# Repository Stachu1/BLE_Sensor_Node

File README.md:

# BLE Sensor Node

**BEng in Electronics Engineering thesis project, focused on low-power design and RF performance.**

A compact, coin-cell-powered Bluetooth Low Energy sensor node that measures temperature and humidity and broadcasts
the data as [BTHome](https://bthome.io/) advertisements, without needing a persistent connection.

*Rev B, `BSN-C23-B`: the top with the printed antenna along the upper edge (left) and the back with the coin-cell
holder (right). 34 × 34 mm.*

## Goal

Keep the average current low enough for multi-year operation on a single CR2032 cell, in a compact size. Main areas
of work: low-power firmware and advertising strategy, antenna/RF performance (chip vs. trace antenna), and power
budgeting around the coin cell's current limits.

## Highlights

- **Two MCUs designed, built and measured side by side** on rev A: Nordic nRF54L05 (`BSN-N54`) and TI CC2340R5
  (`BSN-C23`), with the same sensors, antenna and board outline. The CC2340R5 was chosen for rev B, mainly on sleep
  current and with RF performance as a second factor ([`MCU_DECISION.md`](hardware/MCU_DECISION.md)).
- **4.8 µA average at a 5 s advertising interval, measured** on BSN-C23-A, with firmware that sends one advert
  per sensor reading and writes the new reading into the running advert. Every event (advert, sensor reading,
  payload reload, cold boot) was measured as a charge, which gives a current model for any setting. The model
  predicts 4.9 µA for this case. Sleep floor about 0.7 µA. At 4.8 µA a 225 mAh CR2032 would last about 5 years
  before derating ([power measurements](hardware/C23/testing/rev_A/Power/POWER_MEASUREMENTS.md)).
- **Rev A chip antenna matched on the VNA**, step by step from the unmatched antenna, with the board lifted off the
  bench (the wooden table under it had detuned the antenna) ([antenna matching](hardware/C23/testing/rev_A/RF/ANTENNA_MATCHING.md)).
- **Conducted harmonics measured on a spectrum analyser** and compared with ETSI EN 300 328 (−30 dBm, the
  standard for an EU product) and the stricter FCC restricted-band limit (−41.2 dBm). Formal EMC testing is out
  of scope, so the limits are a reference and results are given as margins. With no filter, H3 at 0 dBm is
  10.6 dB under ETSI and 0.6 dB over FCC on the C23, and 5.7 dB over ETSI on the N54. With the simple pi network
  from TI's reference design the C23 keeps at least 9.5 dB to FCC at +8 dBm. Nordic's reference design uses
  0201 parts. The N54 board uses 0402, so the PA network layout had to be adapted, which likely caused its loss
  of about 10 dB of output power. It was bypassed for the measurements ([C23](hardware/C23/testing/rev_A/RF/RF_CARRIER.md), [N54](hardware/N54/testing/RF/RF_CARRIER.md)).
- **Rev B trace antenna designed in openEMS on the real board, then measured.** A scripted pipeline exports the
  KiCad board (all four copper layers, vias, stack-up, the CR2032) to the FDTD solver on a compute server. The
  chosen inverted-F antenna simulated at −14.9 dB S11 or better across the BLE band with two matching parts. On
  the built board the VNA measured −12.1 dB or better with the simulated parts unchanged, with the resonance
  within 1.5 % of the simulated frequency. The simulated total efficiency is 80 to 91 %, not yet measured
  ([antenna write-up](hardware/C23/testing/RF/antenna_C23-B/README.md), [simulation pipeline](hardware/C23/testing/RF/sim/README.md),
  [VNA measurement](hardware/C23/testing/rev_B/RF/ANTENNA_MATCHING.md)).
- **Nine rev B boards hand-assembled and brought up**, all passing the 13-point hardware self-test. Seven
  have been seen advertising BTHome readings, decoded by a PC script. Rev B RF was checked on a spectrum analyser: carrier within
  ±0.7 ppm of the analyser reference on all three advertising channels, harmonics H2 to H4 below −54 dBm
  ([spectrum](hardware/C23/testing/rev_B/RF/SPECTRUM.md)).
- **Firmware for both MCUs** written to the same structure (bring-up self-test, BLE sensor, CW RF test, one power
  state per build) so the two can be measured the same way.

## Design

| `BSN-C23-B` (TI CC2340R5) | `BSN-N54-A` (Nordic nRF54L05) |
|---|---|
|  |  |
| [Schematic](hardware/C23/schematic.pdf) · [PCB](hardware/C23/PCB.pdf) · [README](hardware/C23/README.md) | [Schematic](hardware/N54/schematic.pdf) · [PCB](hardware/N54/PCB.pdf) · [README](hardware/N54/README.md) |

4-layer, 34 × 34 mm board with an HDC2010 temperature/humidity sensor, the CR2032 holder on the back and test
points for SWD, UART, I2C and the sensor interrupt.

- **Rev A (both variants):** 15.5 mm corner radii (close to round), chip antenna with a pi matching network, an
  optional U.FL connector for conducted RF tests and an SHTC3 footprint as an alternative sensor.
- **Rev B (C23 only):** 10 mm corner radii, an inverted-F antenna printed on the top layer, an MM8130 switch
  connector for VNA measurements of the antenna match, a Tag-Connect footprint for SWD, UART TX and a BOOT pin for
  the ROM bootloader, and a 0 Ω link in the supply for the ammeter. The pi network is unchanged from rev A.

## Status

Rev A of both variants was compared (thesis test T0). **Rev B uses the TI CC2340R5 (`BSN-C23-B`)** with a PCB trace
antenna, and the N54 variant stops at rev A. Rev B was ordered on 2026-11-04 (tag `hw/BSN-C23-B`) and assembled
from 2026-11-13. A rev C will only be made if the rev B tests show it is needed and there is time.

Why the CC2340R5:

- **Lower average current at the intervals this node uses.** The N54 needs 40–50 % less charge per advert and per
  reading, but its 4.2 µA sleep floor outweighs that from about a 1.3 s interval upwards. At 5 s the C23 measured
  4.8 µA and the N54 6.1 µA (table below). The C23 got there in two steps. The first full firmware measured 6.5 µA,
  because in the TI stack every payload reload (stopping the advert, loading the new reading, restarting it) costs
  about 20 µC. The firmware was then changed to skip the reload and write each new reading into the running
  advert, which brought it down to 4.83 µA.
- **A working RF chain.** The C23 keeps a margin to the harmonic limits with the simple pi network from TI's
  reference design, so rev B could start from an RF chain that works. The N54 would need a new harmonic filter and
  another RF iteration.
- **A simpler, cheaper part.** A 4 × 4 mm, 24-pin package against 6 × 6 mm and 48 pins for the nRF54L05, and a
  lower unit price.

Together that made the C23 the simpler and lower-risk base for the next revision.

### Rev B results

The antenna match is measured through an MM8130 switch connector between the chip and the antenna. Plugging in
the probe (right) disconnects the chip side, so the VNA sees only the antenna and its two matching parts, with
no parts moved.

*S11 of the rev B antenna at the MM8130 connector. Left: the antenna without matching parts, openEMS simulation
against measurement. Right: with L2 1.6 nH and L3 6.8 nH from the simulation, measured with the board standing on
its battery holder with the cell, the typical placement. Worst S11 in the BLE band (grey) −18.8 dB.*

The antenna is sensitive to what is around it. Lying flat on a table it is detuned by about 330 MHz. A plastic
enclosure close to the antenna would also lower the resonance, so the match would need retuning in the final
housing. The enclosure is out of scope, as this project covers the electronics and not the mechanical design.

| | `BSN-C23-B` | Notes |
|---|---|---|
| Bring-up | 9 boards, all 13/13 in the hardware self-test | Hand-assembled |
| Antenna match, worst S11 in 2.40–2.48 GHz | −12.1 dB in the air, −18.8 dB standing on the battery holder | Simulated −14.9 dB. Lying flat on a table detunes it by about 330 MHz |
| Carrier frequency | Within ±0.7 ppm of the analyser reference | 2402, 2440 and 2480 MHz, no crystal retrim needed |
| Conducted power at the antenna connector | +3.2 dBm at the +8 dBm setting, −3.9 dBm at the 0 dBm setting | Read +2.4 and −4.7 dBm, corrected for the 0.84 dB probe loss measured on the VNA |
| Harmonics at +8 dBm, conducted | H2 to H4 below −54 dBm. H5 −40.9 dBm: 10.9 dB under ETSI, 0.3 dB under FCC | Probe loss not corrected, the true level is higher. H5 is about 10 dB worse than rev A with the same filter parts, cause not investigated |
| Supply current, continuous carrier at 3.0 V | 6.14 mA at 0 dBm, 14.20 mA at +8 dBm | Sets the coin-cell budget for a radiated test |

Details: [`hardware/C23/README.md`](hardware/C23/README.md), [`hardware/C23/testing/rev_B`](hardware/C23/testing/rev_B).

### Rev A comparison

*Rev A: `BSN-N54-A` (left), `BSN-C23-A` (middle) and the back of `BSN-C23-A` with the coin-cell holder.*

| | `BSN-C23-A` | `BSN-N54-A` |
|---|---|---|
| **Average current, 5 s advertising, measured (model)** | **4.83 µA** (4.9 µA). One advert per sensor reading, reading written into the running advert | **6.1 µA** (6.01 µA). Sensor every 10 s |
| Sleep floor | About 0.7 µA (0.70 µA on the no-filter board, the datasheet typical is 0.71 µA. An early 0.37 µA on board #1 did not repeat) | 4.20 µA (System OFF 2.05 µA, both about 1.4 µA above the datasheet, cause not found) |
| Charge per advert, 0 dBm | 12.6 µC | 7.6 µC |
| Charge per sensor reading, timer / DRDY wake | 9.56 / 3.72 µC | 2.01 / 1.78 µC |
| Charge per payload reload | About 20 µC in the TI stack (6.5 µA at 5 s with a reload every 10 s). Later skipped by writing the reading into the running advert | No such cost |
| Conducted power at the 0 dBm setting, no filter (same spectrum analyser setup, cable loss not corrected) | −1.7 dBm (−3.2 dBm with the pi network) | −0.7 dBm (PA network bypassed) |
| Harmonics with no filter, 0 dBm (conducted, worst is H3) | H3 −40.6 dBm: 10.6 dB under ETSI (−30 dBm), 0.6 dB over FCC (−41.2 dBm) | H3 −24.3 dBm: 5.7 dB over ETSI, 17 dB over FCC |
| Harmonic filter | Pi network from TI's reference design. At +8 dBm (2440 and 2480 MHz) at least 9.5 dB under FCC (H5) | Nordic's reference design uses 0201 parts, this board uses 0402, so the PA network layout was adapted. It lost 10–11 dB of output power, likely because of the adapted layout, and was bypassed. No working filter on this layout |
| Notes | [`hardware/C23/testing`](hardware/C23/testing) | [`hardware/N54/testing`](hardware/N54/testing) |

Rev A boards:

| Board | MCU | Status |
|---|---|---|
| `BSN-N54-A` | nRF54L05 | Ordered and assembled (2 boards). Board #1 advertising BTHome. Board #2 (U.FL): HFXO trimmed to 11.75 pF, PA network bypassed (the rev A layout of it loses 10 dB), 0.0 dBm at the 0 dBm setting. Floor 4.20 µA, 7.6 µC per advert |
| `BSN-C23-A` | CC2340R5 | Ordered and assembled. Board #1 flashed and advertising BTHome, antenna matched with the board lifted off the bench (L2 4.3 nH, L3 2.1 pF). Floor about 0.7 µA, 12.6 µC per advert, about 20 µC per payload reload in the TI stack, 4.83 µA at 5 s with the reading written into the running advert. CW boards with and without the PA pi network |

Open questions:

- The N54 floor sits about 1.4 µA above the datasheet on both boards. Not needed for the MCU choice, but still being
  looked into for the thesis.

### Next

- **Rev B power:** average current on a real CR2032 at a 5 s interval, the VDD dip during TX, and the battery-life
  projection.
- **Range:** line-of-sight range test of the rev A chip antenna and the rev B trace antenna in one session.
- **Radiated:** pattern, total radiated power and the radiated H5 level in the anechoic chamber at the university,
  if a slot can be arranged.
- **Rev C** (optional): only if rev B needs fixes and time allows.

## Repository Structure

```
hardware/
  MCU_DECISION.md   Why rev B uses the CC2340R5
  C23/              BSN-C23 - TI CC2340R5 variant: KiCad project, schematic/PCB PDFs, testing/
  N54/              BSN-N54 - Nordic nRF54L variant (concluded at rev A)
  N52/              BSN-N52 - Nordic nRF52805 side variant: smaller, CR1632 (rev A)
firmware/
  C23/              Firmware for BSN-C23 boards (TI SimpleLink SDK)
  N54/              Firmware for BSN-N54 boards (nRF Connect SDK)
  N52/              Firmware for BSN-N52 boards (nRF Connect SDK, and a bare-metal beacon)
docs/
  datasheets/       Links to the datasheets and application notes used
  images/           Photos
```

The two MCU candidates are different chips (different pinout, power tree and BOM) rather than build options of one
board, so each has its own KiCad project under `hardware/<variant>/` and its own `firmware/<variant>/`. The N54
folders stay as the record of the rev A comparison. Only the C23 variant continues.
`BSN-N52` is a later side variant outside the original requirements: a smaller, cheaper node on a CR1632
with the same sensor and a printed antenna, see [`hardware/N52/README.md`](hardware/N52/README.md).

Test results live next to the board they were measured on, in `hardware/<variant>/testing/`, with the bring-up
procedures in `firmware/<variant>/BRINGUP.md`. The C23 rev A measurements are in `hardware/C23/testing/rev_A/`, the
rev B antenna simulations in `hardware/C23/testing/RF/`. The schematic and PCB PDFs always show the latest revision of each
board. Older revisions are in the KiCad files at their `hw/BSN-<variant>-<rev>` tags.

## Naming Scheme

Each board is identified as **`BSN-<variant>-<revision>`**, e.g. `BSN-C23-A`.

```
BSN-C23-A
 │   │  └─ PCB revision  (A, B, C …)
 │   └──── MCU variant   (C23 = TI CC2340R5, N54 = Nordic nRF54L, N52 = Nordic nRF52805)
 └──────── Board name    (BSN = BLE Sensor Node)
```

- **Variant:** first letter of the MCU part prefix (**n**RF54 → N, **C**C2340 → C) + MCU family number. Each variant
  has its own revision counter.
- **Revision:** bare-PCB revision, bumped only when new boards are ordered. Once gerbers are sent to the fab that
  letter is frozen. The ordered commit is tagged `hw/BSN-<variant>-<rev>`.
- **Assembly option** *(optional)*, e.g. `-UFL`: a population option on the same bare PCB. Does not change the
  revision.
- **Reworked boards** are marked `A*`, with the rework noted in the variant README.
- **The ID is on the board itself:** set in the KiCad title block and printed on the silkscreen. The firmware board
  target is `BSN_C23` / `BSN_N54` / `bsn_n52`.

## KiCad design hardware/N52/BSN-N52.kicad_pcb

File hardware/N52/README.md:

# BSN-N52 (Nordic nRF52805 variant)

> **Side variant, outside the original requirements.** A smaller, cheaper node, designed as a separate
> project ("AirTag") and moved into this repository on 2026-11-23. It uses the same HDC2010 sensor and a printed
> inverted-F antenna like `BSN-C23-B`, but it is smaller, runs on a CR1632 and probably has worse RF performance.
> It does not replace `BSN-C23-B`. Whether and how it appears in the report is still open.

KiCad project: `BSN-N52.kicad_pro`. See the root README for the board naming scheme. Firmware, bring-up procedure
and per-board results: [`firmware/N52`](../../firmware/N52) and [`firmware/N52/BRINGUP.md`](../../firmware/N52/BRINGUP.md).

[Schematic](schematic.pdf) · [PCB](PCB.pdf)

## Rev A (`BSN-N52-A`)

- **24 × 17 mm**, 2 layers, 1.6 mm, 3 mm corner radius. The CR1632 holder is on the back and the cell overhangs
  the bottom edge.
- **nRF52805-CAAA** (WLCSP-28, 2.48 × 2.46 mm, 192 kB flash, 24 kB RAM) with the DC/DC converter (L3 10 µH), a 32 MHz
  crystal and no 32 kHz crystal (the low-frequency clock is the internal RC).
- **HDC2010** temperature/humidity sensor on I2C with its interrupt line (DRDY) to the SoC. No external I2C
  pull-ups (the nRF internal ones are used).
- **Printed meandered inverted-F antenna (MIFA)** along the top edge in a 20 × 5 mm keep-out, designed in openEMS on
  this board ([`testing/RF/sim`](testing/RF/sim)). Fed through a T network L2 4.7 nH series, C1 0.5 pF shunt,
  L1 8.2 nH series (match and harmonic filter, from the r7 simulation with the solder mask and the cell).
  **No RF connector** (no MM8130 or test port): the antenna and the carrier can only be measured radiated, and the
  matching parts and the 32 MHz crystal load caps are fixed in hardware (no firmware trim).
- **SWD only**: Tag-Connect TC2030-NL (J1) with VCC, SWDIO, RESET, SWCLK, GND. No LED, no UART.
- The silkscreen carries the author's handle, not the board ID. The ID is in the KiCad title block only.

### Parts

| Ref | Part | DigiKey |
|---|---|---|
| U2 | Nordic nRF52805-CAAA (WLCSP-28) | `4823-NRF52805-CAAA-RCT-ND` |
| U1 | TI HDC2010 humidity / temperature sensor | `296-47774-1-ND` |
| X1 | ECS ECS-320-8-37B-CKY-TR, 32 MHz, 8 pF, ±10/±10 ppm, 2.0 × 1.6 mm | `50-ECS-320-8-37B-CKY-TRCT-ND` |
| L3 | Murata LQM18DN100M70L, 10 µH, 0603, DC/DC inductor | `490-LQM18DN100M70LCT-ND` |
| C2 | Cal-Chip GMC21X5R476M6R3NT, 47 µF 6.3 V X5R, 0805, bulk cap | `4713-GMC21X5R476M6R3NTCT-ND` |
| BT1 | CR1632 in Assmann A-BAT-CH-C6-EA-CSR1 (the clip is +, a bare pad under the cell is −) | `123-A-BAT-CH-C6-EA-CSR1CT-ND` |
| L2 / C1 / L1 | RF T network: 4.7 nH / 0.5 pF / 8.2 nH | `490-16635-1-ND` / `490-11250-1-ND` / `490-18131-1-ND` |

The BOM export (`BSN-N52.csv`) and the order sheet (`bom/`) are kept locally like those of the other variants.
The schematic is the source.

### Manufacturing

Ordered on 2026-11-16 as a **3 × 3 panel** (KiKit 1.8.1, [`panel/panel.json`](panel/panel.json)), hand assembled,
so no fiducials or tooling holes. The commit that added this folder is tagged `hw/BSN-N52-A`. The board files are
the ordered ones, only renamed and given a title block.

- 2 mm gaps between boards, 5 mm rails top and bottom only.
- Tabs 2.2 mm wide, mouse bites of 3 × 0.5 mm holes at 0.8 mm pitch, **offset −0.5 mm** so the holes sit in the gap
  and not on the antenna. The boards keep an FR4 nub of about 0.25–0.5 mm after breaking (no copper in it).
- The top-edge tabs sit on the antenna edge. Move them off that edge in a later revision if needed.

Regenerate the panel after a board change (from `hardware/N52`):

```
"C:\Program Files\KiCad\10.0\bin\python.exe" -m kikit.ui panelize -p panel/panel.json BSN-N52.kicad_pcb panel/BSN-N52_panel.kicad_pcb
```

### Bring-up status

Three boards assembled, all pass the 11-point hardware self-test (`hwtest`). Details in
[`firmware/N52/BRINGUP.md`](../../firmware/N52/BRINGUP.md). Parts for about seven more are on hand.

| Board | BLE address | Status |
|---|---|---|
| A #1 | DF:55:EE:37:04:CD | `hwtest` 11/11. Used to develop the tests |
| A #2 | C2:D7:6D:9C:B3:20 | A\*: HDC2010 reworked (SDA and INT held low). Then `hwtest` 11/11, `ble_sensor` flashed |
| A #3 | DB:1C:AA:DB:F2:9D | `hwtest` 11/11, BTHome seen on the scanner. `ble_beacon_min` measured at 1.706 µA average |

### Test results

- **Current:** [`testing/Power/POWER_MEASUREMENTS.md`](testing/Power/POWER_MEASUREMENTS.md). 1.706 µA average at
  the 5 s DRDY interval on A #3 with the bare-metal `ble_beacon_min` (System OFF between adverts), about 2.5 times
  lower than `BSN-C23-B` (4.36 to 4.39 µA). Single reading on the 10 mA range, see the caveats there.
- **RF:** simulated only ([`testing/RF/sim`](testing/RF/sim)). Not measured on a built board yet.

### Rework log

Hand-modified boards are marked `A*` (see the root README).

| Board | Date | Change | Reason |
|---|---|---|---|
| A #2 | by 2026-11-23 | HDC2010 (U1) reworked | First `hwtest` failed: SDA and INT held low by U1 (bad joint or short) |

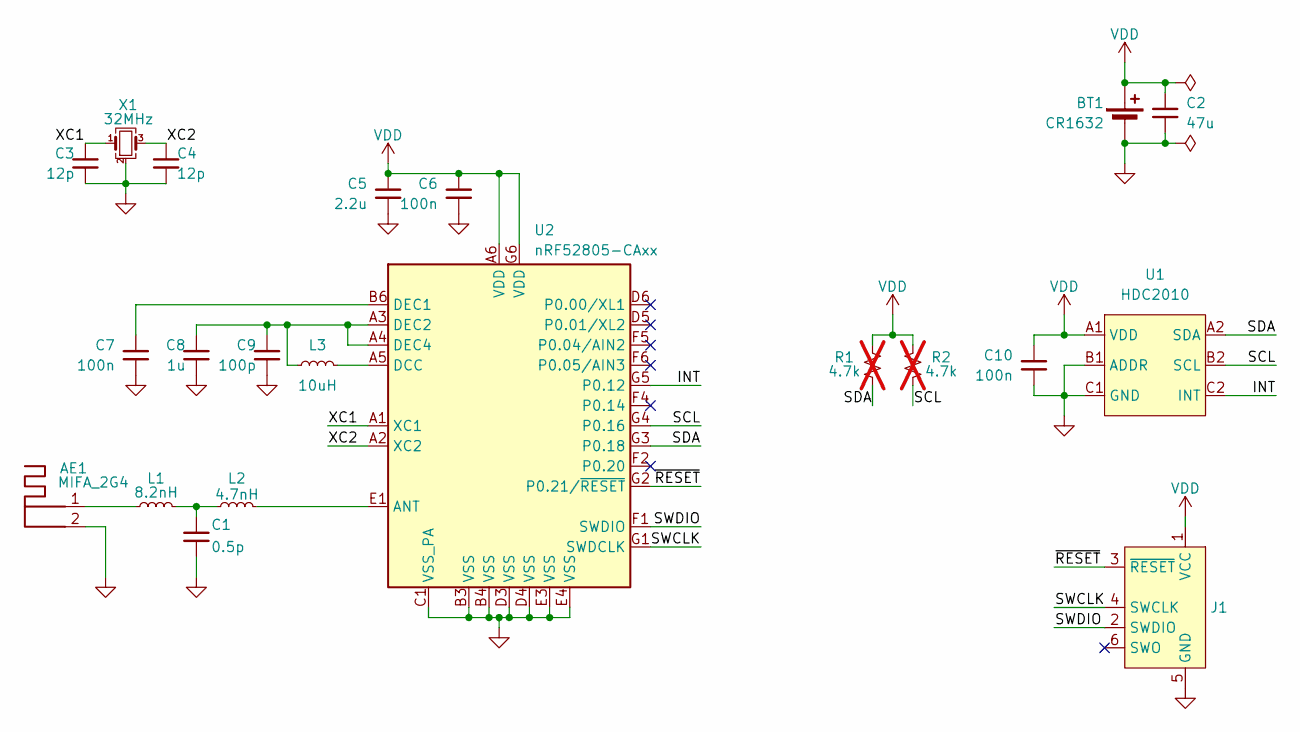
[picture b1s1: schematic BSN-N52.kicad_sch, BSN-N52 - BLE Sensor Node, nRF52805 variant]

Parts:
AE1: MIFA_2G4
BT1: CR1632; BatteryHolder_Assmann_A-BAT-CH-C6-EA-CSR1_CR1632; DigiKey 123-A-BAT-CH-C6-EA-CSR1CT-ND
C1: 0.5p; C_0402_1005Metric; DigiKey 490-11250-1-ND
C2: 47u; C_0805_2012Metric; DigiKey 4713-GMC21X5R476M6R3NTCT-ND
C3, C4: 12p; C_0402_1005Metric; DigiKey 311-1016-1-ND
C5: 2.2u; C_0402_1005Metric; DigiKey 445-9028-1-ND
C6, C7, C10: 100n; C_0402_1005Metric
C8: 1u; C_0402_1005Metric; DigiKey 311-1439-1-ND
C9: 100p; C_0402_1005Metric; DigiKey 311-1024-1-ND
J1: Conn_ARM_SWD_TagConnect_TC2030-NL; Tag-Connect_TC2030-IDC-NL_2x03_P1.27mm_Vertical
L1: 8.2nH; L_0402_1005Metric; DigiKey 490-18131-1-ND
L2: 4.7nH; L_0402_1005Metric; DigiKey 490-16635-1-ND
L3: 10uH; L_0603_1608Metric; DigiKey 490-LQM18DN100M70LCT-ND
R1, R2: 4.7k; R_0402_1005Metric; not fitted
U1: HDC2010; DigiKey 296-47774-1-ND
U2: nRF52805-CAxx; Nordic_nRF52805-CAxx_WLCSP-28_2.482x2.464mm; DigiKey 4823-NRF52805-CAAA-RCT-ND
X1: 32MHz; Crystal_SMD_2016-4Pin_2.0x1.6mm; DigiKey 50-ECS-320-8-37B-CKY-TRCT-ND

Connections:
/INT: U1.C2 (INT), U2.G5 (P0.12)
/SCL: R2.1, U1.B2 (SCL), U2.G4 (P0.16)
/SDA: R1.1, U1.A2 (SDA), U2.G3 (P0.18)
/SWCLK: J1.4 (SWCLK), U2.G1 (SWDCLK)
/SWDIO: J1.2 (SWDIO), U2.F1 (SWDIO)
/XC1: C3.1, U2.A1 (XC1), X1.1
/XC2: C4.1, U2.A2 (XC2), X1.3
/~RESET: J1.3 (~RESET), U2.G2 (P0.21/~RESET)
GND: AE1.2 (GND), BT1.2 (-), C1.2, C2.2, C3.2, C4.2, C5.2, C6.2, C7.2, C8.2, C9.2, C10.2, J1.5 (GND), U1.B1 (ADDR), U1.C1 (GND), U2.B3 (VSS), U2.B4 (VSS), U2.C1 (VSS_PA), U2.D3 (VSS), U2.D4 (VSS), U2.E3 (VSS), U2.E4 (VSS), X1.2 (G), X1.4 (G)
unnamed: AE1.1 (Feed), L1.1
unnamed: C1.1, L1.2, L2.1
unnamed: L2.2, U2.E1 (ANT)
unnamed: L3.2, U2.A5 (DCC)
unnamed: C7.1, U2.B6 (DEC1)
unnamed: C8.1, C9.1, L3.1, U2.A3 (DEC2), U2.A4 (DEC4)
VDD: BT1.1 (+), C2.1, C5.1, C6.1, C10.1, J1.1 (VCC), R1.2, R2.2, U1.A1 (VDD), U2.A6 (VDD), U2.G6 (VDD)

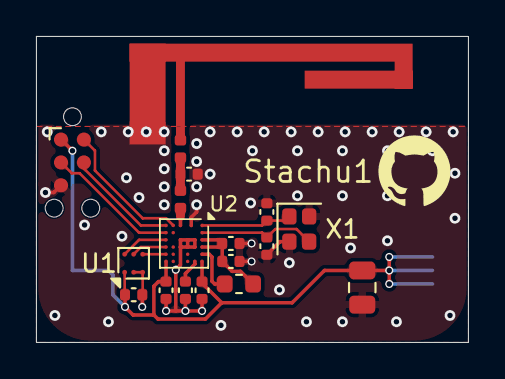
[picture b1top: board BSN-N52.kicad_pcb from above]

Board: 2 copper layers, 24.0 x 17.0 mm, 19 parts (1 on the bottom side), 16 nets.

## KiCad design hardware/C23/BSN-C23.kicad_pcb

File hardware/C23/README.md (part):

# BSN-C23 (TI CC2340R5 variant)

KiCad project: `BSN-C23.kicad_pro`. See the root README for the board naming scheme. The KiCad files, the
schematic and PCB PDFs and the render show rev B. Rev A is at the tag `hw/BSN-C23-A`.

## Rev B (`BSN-C23-B`)

Ordered 2026-11-04 (tag `hw/BSN-C23-B`), nine boards hand-assembled from 2026-11-13. Same 34 × 34 mm, 4-layer board as rev A, with the
changes the rev A tests asked for. Several reference designators changed from rev A, the tables below use the rev B
names.

**Changes from rev A:**

- **Printed inverted-F antenna** (AE1, footprint `IFA_2G4`) on F.Cu along the top edge instead of the chip
  antenna. Designed with openEMS on the real board, see the [antenna write-up](testing/RF/antenna_C23-B/README.md)
  and the [simulation pipeline](testing/RF/sim/README.md). The footprint is generated by
  [`library/gen_ifa_footprint.py`](library/gen_ifa_footprint.py).
- **Corner radius 10 mm** (15.5 mm on rev A). It gives the IFA a straight ground edge of about 14 mm.
- **MM8130 switch connector (J2) instead of the U.FL.** Inserting the probe disconnects the chip side, so the VNA
  sees only the antenna and its match (L2, L3), without moving parts. The 15 pF DC block (C7) stays between the
  chip and J2.
- **Pi network, same parts** (C8, L1, C9, the rev A C7, L1, C8), but the RF path around it is not identical to
  rev A: J2 (MM8130) now sits between the pi network and the antenna, the routing bends, there is no U.FL stub,
  and the vias are placed differently. The rev B harmonics were measured on 2026-11-17 (see
  [`testing/rev_B/RF/SPECTRUM.md`](testing/rev_B/RF/SPECTRUM.md)): H5 is about 10 dB worse than rev A relative
  to the carrier, cause not investigated.
- **0 Ω link R1 in the supply** (VBAT to VDD), with the 2-pin header J1 across it for the ammeter. J4 is a 2-pin
  VDD/GND header for an external supply.
- **Programming and UART:** Tag-Connect TC2030-NL footprint (J3) for SWD. UART TX moved to DIO6, so with RX on
  DIO20 the ROM bootloader works over a plain USB-UART adapter. BOOT pin on DIO3 with a 100 kΩ pull-up (R4) and TP1.
- **LED D1** (with R2 1 kΩ) on DIO4, DNP by default.
- **HDC2010 INT moved from DIO21 to DIO13.** DIO21 is also the ROM bootloader's default trigger pin.
- **Removed:** U2 SHTC3 footprint, X2 (32 kHz crystal) and its load caps, the external 48 MHz load caps (the
  internal HFXT cap array trims X1). The HDC2010 is now U2.

**Population:** DNP = C6 (100 µF), D1, R2, J1, J4. AE1, J3 and the test points are copper only.

**RF network as fitted** (antenna-side values from the simulation, kept after the VNA measurement of 2026-11-13,
see [`testing/rev_B/RF/ANTENNA_MATCHING.md`](testing/rev_B/RF/ANTENNA_MATCHING.md)):

| Ref | Value | Part | Function |
|---|---|---|---|
| C8, C9 | 1.5 pF | 490-8087-1-ND | Pi network, shunt (as rev A) |
| L1 | 2.8 nH | LQW15AN2N8G80D | Pi network, series (as rev A) |
| C7 | 15 pF | 490-11191-1-ND | DC block |
| J2 | MM8130-2600RA2 | 490-4981-1-ND | Switch connector, VNA probe on the antenna side |
| L2 | 1.6 nH | LQG15WZ1N6B02D | Antenna match, series |
| L3 | 6.8 nH | LQW15AN6N8G80D | Antenna match, shunt at J2 |
| AE1 | IFA | `IFA_2G4` (printed) | Antenna |

**Pin map** (CC2340R5 VQFN-24):

| Signal | DIO | Pin | Test point | Change from rev A |
|---|---|---|---|---|
| I2C SDA | DIO12 | 5 | TP3 | |
| I2C SCL | DIO24 | 12 | TP9 | |
| HDC2010 INT | DIO13 | 6 | TP4 | was DIO21 |
| UART TX | DIO6 | 19 | TP2 | was DIO13 |
| UART RX | DIO20 | 9 | TP8 | |
| BOOT | DIO3 | 14 | TP1 | new |
| LED | DIO4 | 15 | | new |
| SWDIO / SWCLK | DIO16 / DIO17 | 7 / 8 | TP5 / TP7 | |
| nRESET | | 13 | TP6 | |

### Rev B boards and rework log

Bring-up details per board are in [`BRINGUP.md`](../../firmware/C23/BRINGUP.md). Measurements are in
[`testing/rev_B`](testing/rev_B).

| Board | Built as | Rework | Self-test | Use |
|---|---|---|---|---|
| B #1 | No 100 µF cap, J2 to the antenna, no R1 (supply through the J1 jumper) | 2026-11-13: L2 0 Ω and L3 open for the bare-antenna sweep, then L2 1.6 nH and L3 6.8 nH fitted | 13/13 (2026-11-16) | Antenna without parts, current measurements |
| B #2 | One 100 µF cap, J2 to the antenna, no R1 | 2026-11-19: battery holder torn off, solder mask scraped and the holder soldered back on. Pi network removed: C8 and C9 off, L1 bridged with solder. Later the same day the pi network refitted (C8, C9 1.5 pF, L1 2.8 nH, bridge removed) | 13/13 (2026-11-13), not repeated after the rework | VNA match with L2 1.6 nH and L3 6.8 nH. Radiated pattern and harmonics in the chamber (2026-11-19), with and without the pi network |
| B #3 | Two 100 µF caps, J2 rotated 180° about the axis normal to the board, so the probe sees the PA side and disconnects the antenna, no R1 | 2026-11-13: L2 1.6 nH and L3 6.8 nH fitted | 13/13 (2026-11-16) | Continuous carrier: conducted power, harmonics, supply current |
| B #4 | One 100 µF cap, J2 to the antenna, R1 0 Ω | 2026-11-16: U2 (HDC2010) replaced after a hand-soldering fault found by `hwtest` | 13/13 (2026-11-16) | `ble_sensor` |
| B #5 to B #9 | One 100 µF cap, J2 to the antenna, R1 0 Ω | – | 13/13 (2026-11-16) | `ble_sensor` |

All nine boards have L2 1.6 nH and L3 6.8 nH. B #1 to B #3 run from the coin cell only with the jumper on J1.

## Rev A (`BSN-C23-A`)

This project started as a copy of `BSN-N54-A` (board outline, power, sensors, antenna and
test points), with the MCU, power tree, 48 MHz crystal, RF network and SWD pins replaced for the
CC2340R5. Rev A was exported and ordered as a separate design (not panelized).

**Population:** DNP = U2 (SHTC3), X2 (32 kHz, LFOSC is used instead), C9, C14, C15, C16, C19, C20,
J1 (U.FL), L4. Everything else is fitted.

**RF network as fitted** (π network C7, C8, L1 from the TI reference design, L2 and L3 from the evaluation board in the
AANI-CH-0138-Q datasheet, not tuned for this board):

| Ref | Value | Part |
|---|---|---|
| C7, C8 | 1.5 pF | 490-8087-1-ND |
| L1 | 2.8 nH | LQW15AN2N8G80D |
| C6 | 15 pF | 490-11191-1-ND |
| L2 | 6.7 nH | LQW15AN6N7B00D |
| L3 | 7.3 nH | 490-6844-1-ND |
| AE1 | Chip antenna | AANI-CH-0138-Q-T |

**Tuned antenna match** (VNA, board lifted off the bench, see below): L2 = **4.3 nH**, **2.1 pF** on the
L3 pads instead of the 7.3 nH. Fitted on board #1 (2026-10-26).

### Bring-up status

Procedure and per-board results: [`firmware/C23/BRINGUP.md`](../../firmware/C23/BRINGUP.md).

| Board | BLE address | Status |
|---|---|---|
| #1 | FC:DE:C5:73:2F:4E | Flashes over SWD. `hwtest` 13/13 PASS. `ble_sensor` advertises BTHome and readings are received on the PC with `tools/bsn_scan.py`. A\*: antenna side matched (L2 4.3 nH, 2.1 pF on the L3 pads). **U2 (SHTC3) is fitted.** Floor 0.366 µA on 2026-10-26, 0.94 µA on 2026-11-10 (cause not found), 16.1 µA with 1 s advertising, see [Current measurements](#current-measurements). |
| RF test | (no MCU) | Antenna-only board used for VNA matching, see below. |
| RF CW | | MCU, X1, pi network (C7/L1/C8) and J1 only, no antenna. Used with `cwtest` for the carrier frequency and output power, see [`testing/rev_A/RF/RF_CARRIER.md`](testing/rev_A/RF/RF_CARRIER.md): HFXT trim set to 44 (+2.2 ppm), +6.7 dBm at the +8 dBm setting. |
| RF CW no-pi | | As RF CW, but with the PA-side pi network removed (see the rework log). `hwtest` PASS. For the conducted power and harmonics comparison with RF CW. |

### Current measurements

Full notes and data: [`testing/rev_A/Power/POWER_MEASUREMENTS.md`](testing/rev_A/Power/POWER_MEASUREMENTS.md).

Board #1 at 3.0 V: sleep floor **0.366 µA** (with or without the BLE stack). This did not repeat: on 2026-11-10 board #1 read 0.94 µA and the no-pi board 0.70 µA, close to the datasheet typical of 0.71 µA, so the floor is taken as about 0.7 µA. With one advert per sensor reading and the reading written into the running advert, the average at 5 s is **4.83 µA** (model 4.9 µA). One advertising event at 0 dBm costs
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
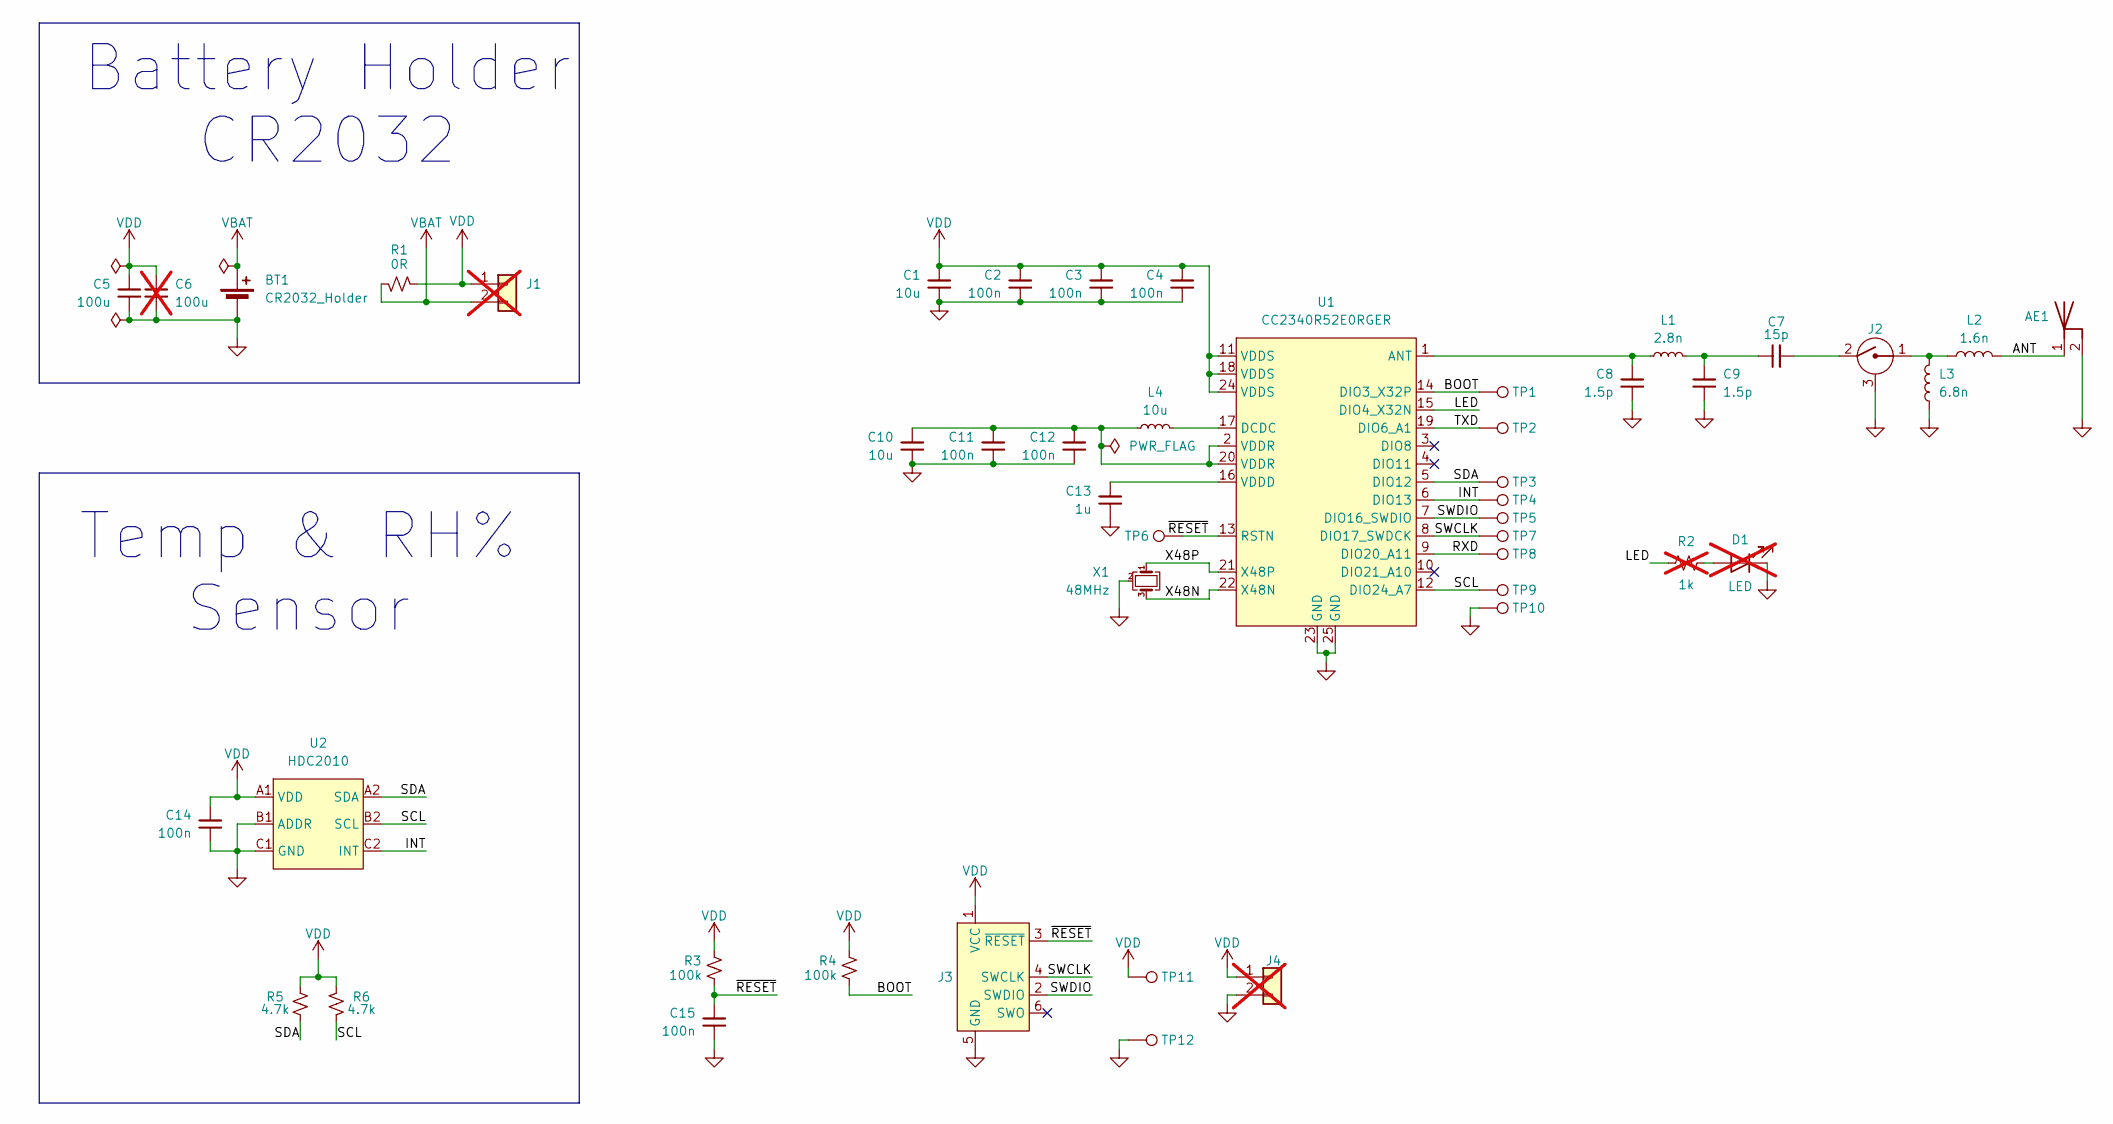
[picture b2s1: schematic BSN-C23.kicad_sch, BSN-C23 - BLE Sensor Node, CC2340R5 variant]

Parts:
AE1: IFA_2G4
BT1: CR2032_Holder; BatteryHolder_Renata_SMTU2032-LF_1x2032; DigiKey 123-A-BAT-CH-C8-EA-ZSR3CT-ND
C1, C10: 10u; C_0603_1608Metric
C2, C3, C4, C11, C12, C14, C15: 100n; C_0402_1005Metric
C5: 100u; C_0805_2012Metric; DigiKey 490-GRM21BR60J107ME15KCT-ND
C6: 100u; C_0805_2012Metric; DigiKey 490-GRM21BR60J107ME15KCT-ND; not fitted
C7: 15p; C_0402_1005Metric; DigiKey 490-11191-1-ND
C8, C9: 1.5p; C_0402_1005Metric; DigiKey 490-8087-1-ND
C13: 1u; C_0402_1005Metric
D1: LED; LED_0603_1608Metric; DigiKey 475-LOQ976.01-P2R2-25-1-20-R18CT-ND; not fitted
J1, J4: Conn_01x02; PinHeader_1x02_P2.00mm_Vertical; DigiKey 952-2273-ND; not fitted
J2: MM8130-2600RA2; Murata_MM8130-2600; DigiKey 490-4981-1-ND
J3: Conn_ARM_SWD_TagConnect_TC2030-NL; Tag-Connect_TC2030-IDC-NL_2x03_P1.27mm_Vertical
L1: 2.8n; L_0402_1005Metric; DigiKey 490-LQW15AN2N8G80DCT-ND
L2: 1.6n; L_0402_1005Metric; DigiKey 490-LQG15WZ1N6B02DCT-ND
L3: 6.8n; L_0402_1005Metric; DigiKey 490-14714-1-ND
L4: 10u; L_0603_1608Metric
R1: 0R; R_0402_1005Metric; DigiKey P0.0JCT-ND
R2: 1k; R_0402_1005Metric; not fitted
R3, R4: 100k; R_0402_1005Metric
R5, R6: 4.7k; R_0402_1005Metric
TP1, TP2, TP3, TP4, TP5, TP6, TP7, TP8, TP9, TP10, TP11, TP12: TestPoint; TestPoint_Pad_D1.0mm
U1: CC2340R52E0RGER; Texas_RGE0024B_VQFN-24-1EP_4x4mm_P0.5mm_EP2.45x2.45mm_Therm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; DigiKey 296-CC2340R52E0RGERCT-ND
U2: HDC2010; DigiKey 296-47774-1-ND
X1: 48MHz; Crystal_SMD_3225-4Pin_3.2x2.5mm; DigiKey 50-ECS-480-8-33B-CWN-TR3CT-ND

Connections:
/ANT: AE1.1 (Feed), L2.2
/BOOT: R4.1, TP1.1 (1_1), U1.14 (DIO3_X32P)
/INT: TP4.1 (1_1), U1.6 (DIO13), U2.C2 (INT)
/LED: R2.1, U1.15 (DIO4_X32N)
/RXD: TP8.1 (1_1), U1.9 (DIO20_A11)
/SCL: R6.1, TP9.1 (1_1), U1.12 (DIO24_A7), U2.B2 (SCL)
/SDA: R5.1, TP3.1 (1_1), U1.5 (DIO12), U2.A2 (SDA)
/SWCLK: J3.4 (SWCLK), TP7.1 (1_1), U1.8 (DIO17_SWDCK)
/SWDIO: J3.2 (SWDIO), TP5.1 (1_1), U1.7 (DIO16_SWDIO)
/TXD: TP2.1 (1_1), U1.19 (DIO6_A1)
/X48N: U1.22 (X48N), X1.3
/X48P: U1.21 (X48P), X1.1
/~RESET: C15.1, J3.3 (~RESET), R3.1, TP6.1 (1_1), U1.13 (RSTN)
GND: AE1.2 (GND), BT1.2 (-), C1.2, C2.2, C3.2, C4.2, C5.2, C6.2, C8.2, C9.2, C10.2, C11.2, C12.2, C13.2, C14.2, C15.2, D1.1 (K), J2.3, J3.5 (GND), J4.2, L3.1, TP10.1 (1_1), TP12.1 (1_1), U1.23 (GND), U1.25 (GND), U2.B1 (ADDR), U2.C1 (GND), X1.2 (G), X1.4 (G)
unnamed: C7.1, J2.2
unnamed: C7.2, C9.1, L1.2
unnamed: C10.1, C11.1, C12.1, L4.1, U1.2 (VDDR), U1.20 (VDDR)
unnamed: D1.2 (A), R2.2
unnamed: J2.1, L2.1, L3.2
unnamed: C8.1, L1.1, U1.1 (ANT)
unnamed: L4.2, U1.17 (DCDC)
unnamed: C13.1, U1.16 (VDDD)
VBAT: BT1.1 (+), J1.2, R1.1
VDD: C1.1, C2.1, C3.1, C4.1, C5.1, C6.1, C14.1, J1.1, J3.1 (VCC), J4.1, R1.2, R3.2, R4.2, R5.2, R6.2, TP11.1 (1_1), U1.11 (VDDS), U1.18 (VDDS), U1.24 (VDDS), U2.A1 (VDD)

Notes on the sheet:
Battery Holder CR2032
Temp & RH% Sensor

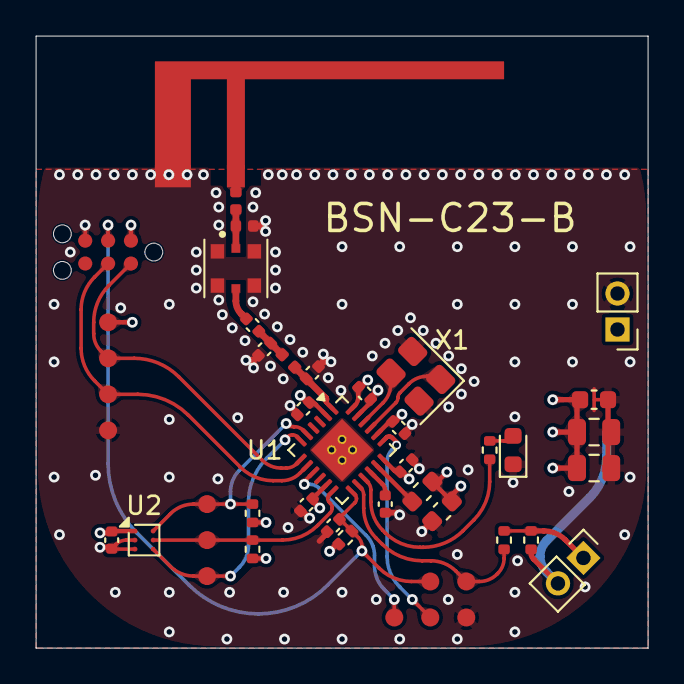
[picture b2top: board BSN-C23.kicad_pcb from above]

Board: 4 copper layers, 34.0 x 34.0 mm, 47 parts (1 on the bottom side), 24 nets.

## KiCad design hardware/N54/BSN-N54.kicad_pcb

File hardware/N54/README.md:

# BSN-N54 (Nordic nRF54L variant)

> **Concluded at rev A.** The N54 was compared with the C23 on rev A, and rev B uses the CC2340R5. See
> [`MCU_DECISION.md`](../MCU_DECISION.md). This folder is kept as the record of that comparison.

KiCad project: `BSN-N54.kicad_pro`. See the root README for the board naming scheme.

## Rev A (`BSN-N54-A`)

Ordered as a separate design from BSN-C23-A (not panelized). Firmware, bring-up procedure and per-board
results: [`firmware/N54`](../../firmware/N54) and [`firmware/N54/BRINGUP.md`](../../firmware/N54/BRINGUP.md).

### Bring-up status

| Board | BLE address | Status |
|---|---|---|
| #1 | EC:A6:80:CE:7A:1A | Full build except U2 (SHTC3) and X2 (32 kHz). `hwtest` 13/13 PASS. `ble_sensor` advertises BTHome and is decoded with `tools/bsn_scan.py`. Antenna side fitted with the C23 values (L6 4.3 nH, 2.1 pF shunt), **not verified on this layout** (see below). PA network as designed, which loses about 10 dB (see board #2). |
| #2 | FA:28:B5:E0:85:F5 | MCU + U.FL, no antenna, no U2/X2. `hwtest` 13/13 PASS. A\*: PA network bypassed. Used for the crystal trim, conducted power and the current measurements. |

### Test results

- **RF:** [`testing/RF/RF_CARRIER.md`](testing/RF/RF_CARRIER.md). HFXO trim 11.75 pF (+127 ppm at the datasheet
  7 pF). The reference PA network as laid out costs 10–11 dB. Bypassed, the PA gives 0.0 dBm at the 0 dBm
  setting and +7.5 dBm at +8 dBm.
- **Current:** [`testing/Power/POWER_MEASUREMENTS.md`](testing/Power/POWER_MEASUREMENTS.md). Floor 4.20 µA
  (System OFF 2.05 µA, both about 1.4 µA above the datasheet on both boards, cause not found), 7.6 µC per advert
  at 0 dBm, 2.01 / 1.78 µC per sensor reading with timer / DRDY wake (C23: 0.366 µA, 12.6 µC, 9.56 / 3.72 µC).

### Rework log

Hand-modified boards are marked `A*` (see the root README).

| Board | Date | Change | Reason |
|---|---|---|---|
| #1 | 2026-10-27 | Antenna side: 4.3 nH series and 2.1 pF shunt (the C23 match) | Same antenna as C23. Not re-matched: AE1 is fed from the other end than on C23 (rotated 180°, feed pad at x = 146.75 instead of 153.25) through a longer trace, so the match is only a starting point |
| #2 | 2026-10-27 | X1 reflowed | Checking the +127 ppm offset (no change) |
| #2 | 2026-10-27 | PA network bypassed: 15 pF in series at L2 (DC block), L3 and L4 bridged, C14, C15, C16 removed. R4 0 Ω and J1 kept | The network cost 10–11 dB. Bypassed, the output matches the datasheet |
| #2 | 2026-10-27 | Cleaned with IPA | Checking whether flux explains the high floor current (no change) |

## ANT-pin matching network

The antenna matching network on the nRF54L05 ANT pin (U1 pin 31) is the Nordic reference PA network (nRF54L
datasheet, circuit configuration 1 for QFN48: L2, C14, L3, C15, L4, C16), followed by the antenna match (L5, L6, L7)
and the U.FL test point (R4, J1).

```
U1.ANT(31) ─ L2 ─┬─ L3 ─┬─ L4 ─┬──────────── L6 ─┬─ AE1
               C14    C15    C16   L5      │     L7
                │      │      │    │      R4     │
              VSS_PA  GND    GND  GND      │    GND
             (pin 32)                     J1
```

| Ref | Value | Role |
|---|---|---|
| L2, C14, L3, C15, L4, C16 | 2.7 nH, 1.5 pF, 3.5 nH, 2.0 pF, 3.5 nH, 0.3 pF | Nordic reference PA network (0201 in the reference, 0402 here) |
| L5 | 7.3 nH | Shunt to GND on the J1 node (antenna side) |
| L6 | 6.7 nH | Series to the antenna |
| L7 | | Shunt at the antenna feed |
| R4, J1 | 0 Ω, U.FL | Test point, not fitted in normal use |

C14 grounds only to pin 32 (VSS_PA), which only joins the centre pad, and C15 grounds straight to the bottom plane
with no inner-layer fill, as Nordic's notes require.

**Measured on rev A:** this network, as laid out with 0402 parts, cost 10–11 dB into 50 Ω (see
[`testing/RF/RF_CARRIER.md`](testing/RF/RF_CARRIER.md)). A rev B N54 should copy Nordic's 0201 layout exactly and
verify the PA network into 50 Ω on its own before the antenna is matched.

### Original Smith chart estimate (superseded)

Before the boards existed, the MCU source impedance and the antenna impedance were estimated from the nRF54L and
antenna datasheets and stepped through all 8 elements on a Smith chart. This treated L5 as a series part, which it
isn't on the board, and the estimated antenna impedance was later measured on C23 to be quite different
(about 6.4 − j13 Ω, see `hardware/C23/testing/rev_A/RF/ANTENNA_MATCHING.md`). Kept for reference:

https://onlinesmithchart.com/?circuit=blackBox_34.1_-40.9_0__seriesInd_2.7_nH_0_0__shortedCap_1.5_pF_0_0_0__seriesInd_3.5_nH_0_0__shortedCap_2_pF_0_0_0__seriesInd_3.5_nH_0_0__shortedCap_0.3_pF_0_0_0__shortedInd_7.3_nH_0_0__seriesInd_6.7_nH_0_0&fSpan=0

A simplified 3-element equivalent from the same estimate:

https://onlinesmithchart.com/?circuit=blackBox_34.1_-40.9_0__seriesInd_4.2_nH_0_0__shortedCap_0.3_pF_0_0_0__seriesInd_6.7_nH_0_0&fSpan=0

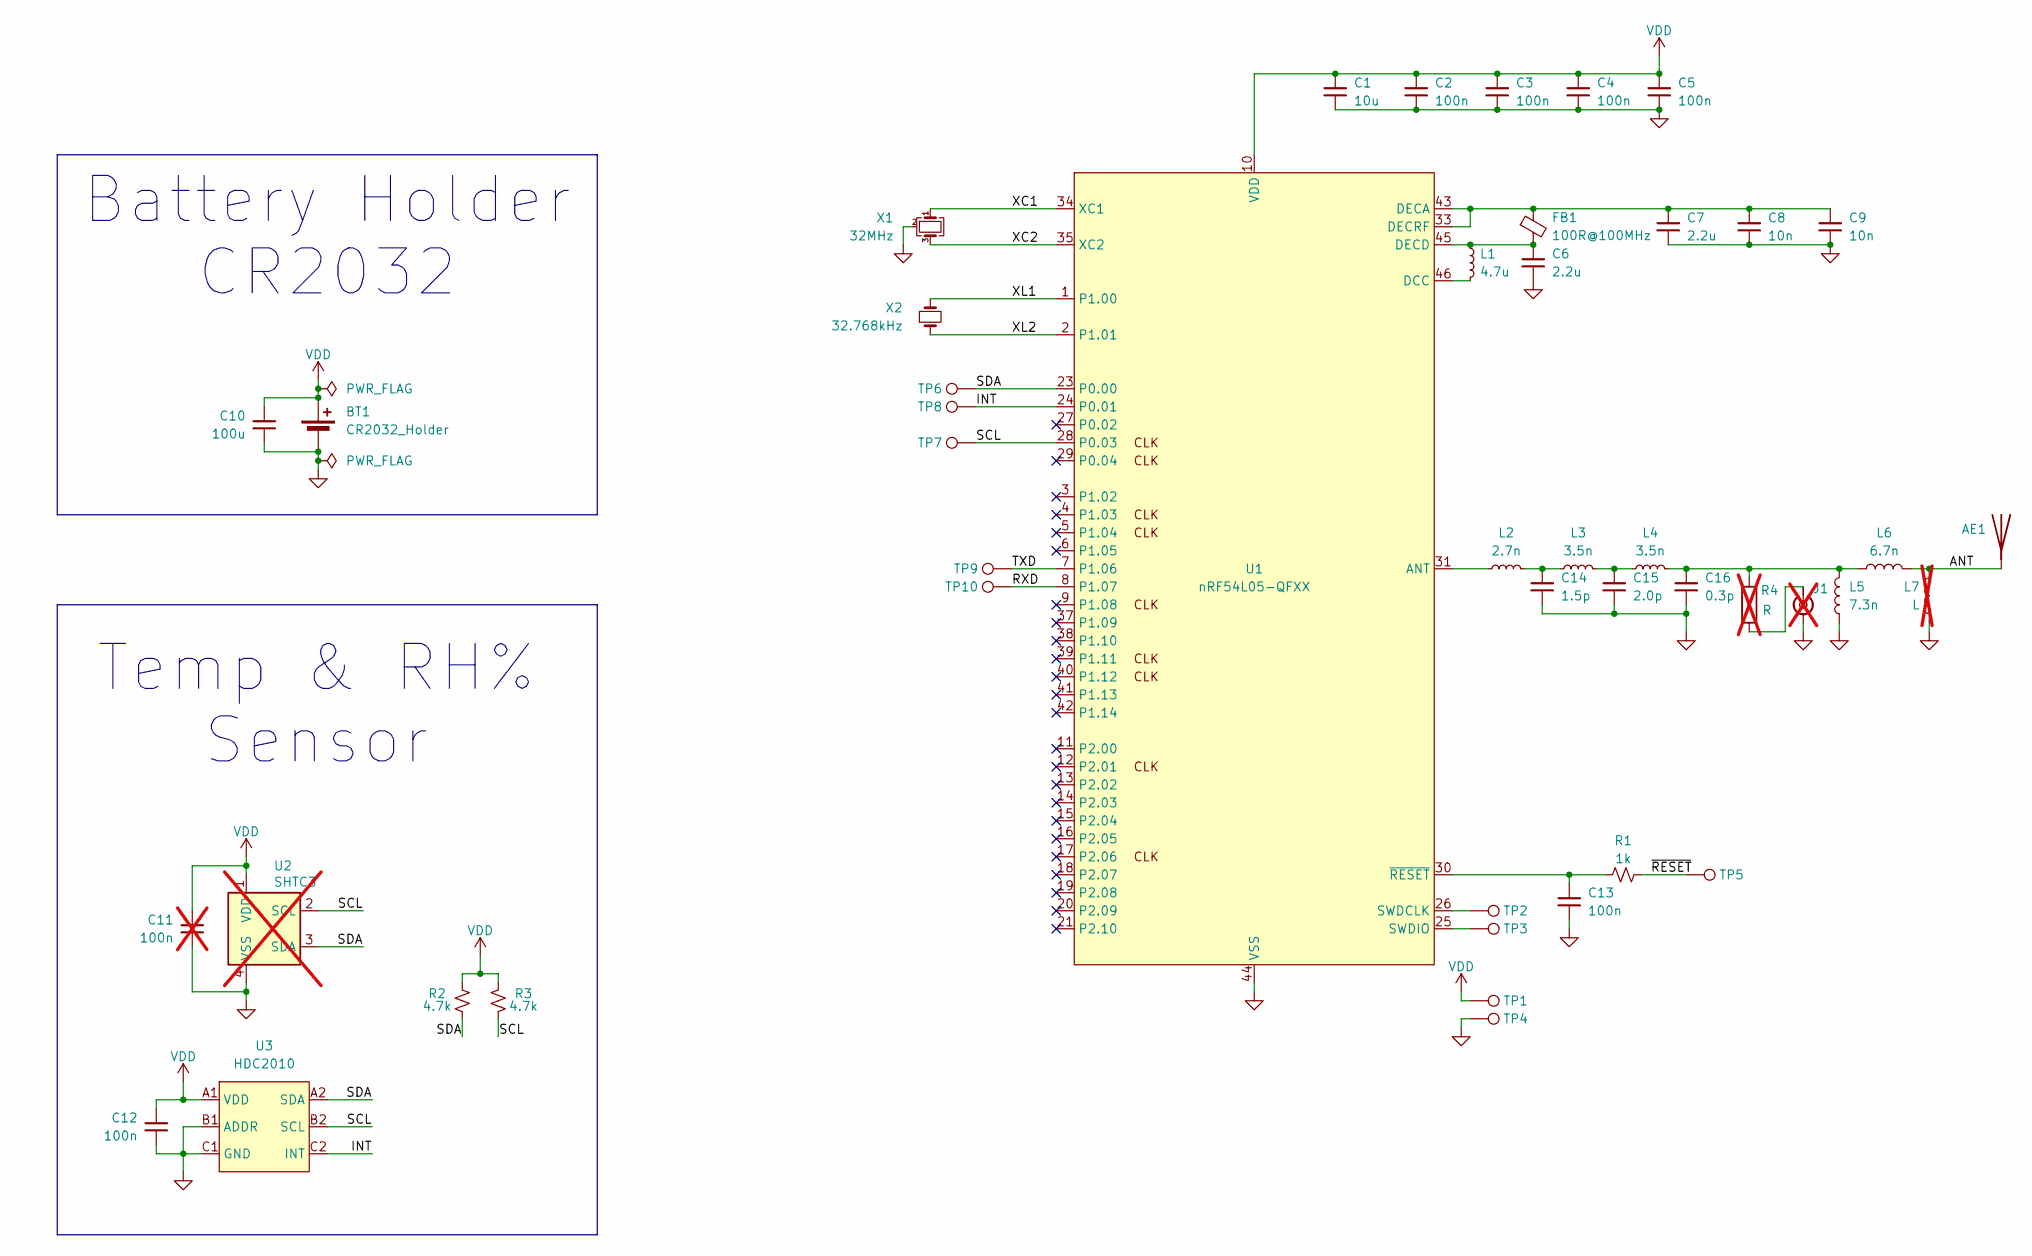
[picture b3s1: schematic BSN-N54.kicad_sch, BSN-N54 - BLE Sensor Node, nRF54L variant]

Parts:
AE1: AANI-CH-0138-Q-T; DigiKey 535-AANI-CH-0138-Q-TCT-ND
BT1: CR2032_Holder; BatteryHolder_Renata_SMTU2032-LF_1x2032; DigiKey 123-A-BAT-CH-C8-EA-ZSR3CT-ND
C1: 10u; C_0603_1608Metric
C2, C3, C4, C5, C12, C13: 100n; C_0402_1005Metric
C6, C7: 2.2u; C_0402_1005Metric; DigiKey 445-9028-1-ND
C8, C9: 10n; C_0402_1005Metric; DigiKey 490-4516-1-ND
C10: 100u; C_0805_2012Metric; DigiKey 490-GRM21BR60J107ME15KCT-ND
C11: 100n; C_0402_1005Metric; not fitted
C14: 1.5p; C_0402_1005Metric; DigiKey 490-8087-1-ND
C15: 2.0p; C_0402_1005Metric; DigiKey 490-11205-1-ND
C16: 0.3p; C_0402_1005Metric; DigiKey 490-11248-1-ND
FB1: 100R@100MHz; L_0603_1608Metric
J1: Conn_Coaxial_Small; U.FL_Hirose_U.FL-R-SMT-1_Vertical; DigiKey H11891CT-ND; not fitted
L1: 4.7u; L_0603_1608Metric; DigiKey 490-12065-1-ND
L2: 2.7n; L_0402_1005Metric; DigiKey 490-15398-1-ND
L3, L4: 3.5n; L_0402_1005Metric; DigiKey 490-15430-1-ND
L5: 7.3n; L_0402_1005Metric; DigiKey 490-6844-1-ND
L6: 6.7n; L_0402_1005Metric; DigiKey 490-LQW15AN6N7B00DCT-ND
L7: L; L_0402_1005Metric; not fitted
R1: 1k; R_0402_1005Metric
R2, R3: 4.7k; R_0402_1005Metric
R4: R; R_0201_0603Metric; not fitted
TP1, TP2, TP3, TP4: TestPoint; TestPoint_Pad_D1.5mm
TP5, TP6, TP7, TP8, TP9, TP10: TestPoint; TestPoint_Pad_D1.0mm
U1: nRF54L05-QFXX; VQFN-48-1EP_6x6mm_P0.4mm_EP4.1x4.1mm_ThermalVias; DigiKey 4823-NRF54L05-QFAA-RCT-ND
U2: SHTC3; Sensirion_DFN-4-1EP_2x2mm_P1mm_EP0.7x1.6mm; DigiKey 1649-SHTC3-TR-2.5KSCT-ND; not fitted
U3: HDC2010; DigiKey 296-47774-1-ND
X1: 32MHz; Crystal_SMD_3225-4Pin_3.2x2.5mm; DigiKey 478-CX3225FB32000C0FZZH1CT-ND
X2: 32.768kHz; Crystal_SMD_3215-2Pin_3.2x1.5mm; DigiKey 728-1074-1-ND

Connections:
/ANT: AE1.1 (Feed_1), L6.2, L7.1
/INT: TP8.1 (1_1), U1.24 (P0.01), U3.C2 (INT)
/RXD: TP10.1 (1_1), U1.8 (P1.07)
/SCL: R3.1, TP7.1 (1_1), U1.28 (P0.03), U2.2 (SCL), U3.B2 (SCL)
/SDA: R2.1, TP6.1 (1_1), U1.23 (P0.00), U2.3 (SDA), U3.A2 (SDA)
/TXD: TP9.1 (1_1), U1.7 (P1.06)
/XC1: U1.34 (XC1), X1.1
/XC2: U1.35 (XC2), X1.3
/XL1: U1.1 (P1.00), X2.2
/XL2: U1.2 (P1.01), X2.1
/~RESET: R1.2, TP5.1 (1_1)
GND: BT1.2 (-), C1.2, C2.2, C3.2, C4.2, C5.2, C6.2, C7.2, C8.2, C9.2, C10.2, C11.2, C12.2, C13.2, C14.2, C15.2, C16.2, J1.2 (Ext), L5.1, L7.2, TP4.1 (1_1), U1.32 (VSS_PA), U1.44 (VSS), U1.49 (VSS), U2.4 (VSS), U3.B1 (ADDR), U3.C1 (GND), X1.2 (G), X1.4 (G)
unnamed: C14.1, L2.2, L3.1
unnamed: C15.1, L3.2, L4.1
unnamed: C16.1, L4.2, L5.2, L6.1, R4.1
unnamed: J1.1 (In), R4.2
unnamed: L2.1, U1.31 (ANT)
unnamed: L1.2, U1.46 (DCC)
unnamed: C7.1, C8.1, C9.1, FB1.1, U1.33 (DECRF), U1.43 (DECA)
unnamed: C6.1, FB1.2, L1.1, U1.45 (DECD)
unnamed: TP2.1 (1_1), U1.26 (SWDCLK)
unnamed: TP3.1 (1_1), U1.25 (SWDIO)
unnamed: C13.1, R1.1, U1.30 (~RESET)
VDD: BT1.1 (+), C1.1, C2.1, C3.1, C4.1, C5.1, C10.1, C11.1, C12.1, R2.2, R3.2, TP1.1 (1_1), U1.10 (VDD), U1.22 (VDD), U1.36 (VDD), U1.47 (VDD), U1.48 (VDD), U2.1 (VDD), U3.A1 (VDD)

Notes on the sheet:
Battery Holder CR2032
Temp & RH% Sensor

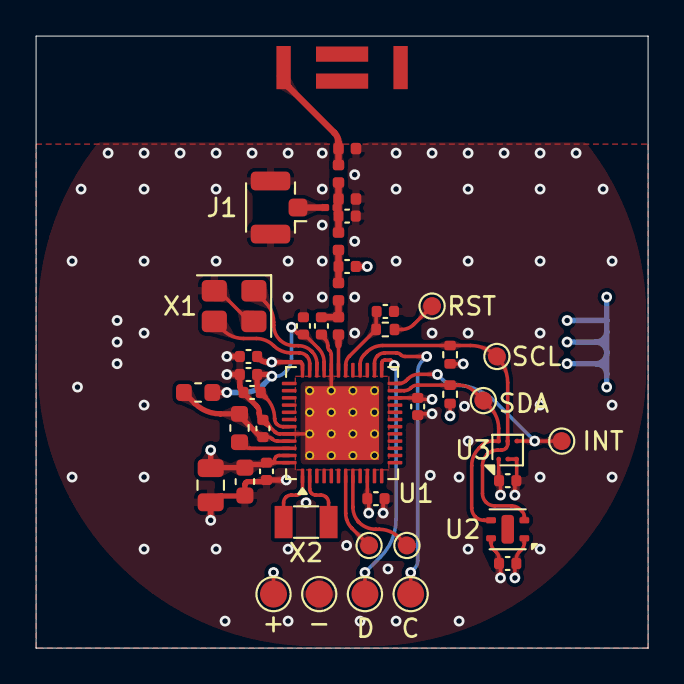
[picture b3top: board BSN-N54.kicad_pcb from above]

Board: 4 copper layers, 34.0 x 34.0 mm, 46 parts (1 on the bottom side), 24 nets.

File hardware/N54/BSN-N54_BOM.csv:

"Reference","Qty","Value","DigiKey","AX"
"AE1","1","AANI-CH-0138-Q-T","535-AANI-CH-0138-Q-TCT-ND",""
"BT1","1","CR2032_Holder","123-A-BAT-CH-C8-EA-ZSR3CT-ND",""
"C1","1","10u","","27204"
"C2,C3,C4,C5,C12,C13","6","100n","","27726"
"C6,C7","2","2.2u","490-12731-1-ND",""
"C8,C9","2","10n","490-3194-1-ND",""
"C10","1","100u","490-9969-1-ND",""
"C14","1","1.5p","490-8087-1-ND",""
"C15","1","2.0p","490-11205-1-ND",""
"C16","1","0.3p","490-17132-1-ND",""
"FB1","1","100R@100MHz","","73236"
"J1","1","Conn_Coaxial_Small","H11891CT-ND",""
"L1","1","4.7u","490-12065-1-ND",""
"L2","1","2.7n","490-15398-1-ND",""
"L3,L4","2","3.5n","490-15430-1-ND",""
"L5","1","7.3n","490-6844-1-ND",""
"L6","1","6.7n","490-LQW15AN6N7B00DCT-ND",""
"R1","1","1k","","201001"
"R2,R3","2","4.7k","","204701"
"U1","1","nRF54L05-QFXX","4823-NRF54L05-QFAA-RCT-ND",""
"U2","1","SHTC3","1649-SHTC3-TR-2.5KSCT-ND",""
"U3","1","HDC2010","296-47774-1-ND",""
"X1","1","32MHz","478-CX3225FB32000C0FZZH1CT-ND",""
"X2","1","32.768kHz","728-1074-1-ND",""
